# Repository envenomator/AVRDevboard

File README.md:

I bought the book 'Make: AVR Programming - by Elliot Williams' and soon got fed up breadboarding the experiments.
So I created an PCB-based development board for Atmega328p, with basics like 

8x LED on PB0-7
LDR / Potmeter
Servo header / servo power selector 
Two pushbuttons, one at each INT0/1
I2C header 
Serial header 

Several jumpers, to make optimal use of pins.

Selections via jumpers:
1) Use either crystal or LEDs on PB6/7
2) Use either LDR or Potmeter at PC0
3) Use either Servo or LED at PB1 / T1 16-bit timer OC1A
4) Use either VCC voltage for servo, or seperately supplied voltage

PINs available for
1) I2C
2) Serial GND/TX/RX
3) INT0/INT1

Photo shows an earlier PCB with switched labels. Current gerbers are correct and have been printed correctly at JLCPCB.

Enjoy experimenting!

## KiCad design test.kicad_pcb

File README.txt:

A development board for Atmega328p, with basics like 

8x LED on PB0-7
LDR / Potmeter
Servo header / servo power selector 
Two pushbuttons, one at each INT0/1
I2C header 
Serial header 

Several jumpers, to make optimal use of pins.

Selections via jumpers:
1) Use either crystal or LEDs on PB6/7
2) Use either LDR or Potmeter at PC0
3) Use either Servo or LED at PB1 / T1 16-bit timer OC1A
4) Use either VCC voltage for servo, or seperately supplied voltage

PINs available for
1) I2C
2) Serial GND/TX/RX
3) INT0/INT1

Photo shows an earlier PCB with switched labels. Current gerbers are correct and have been printed correctly at JLCPCB.

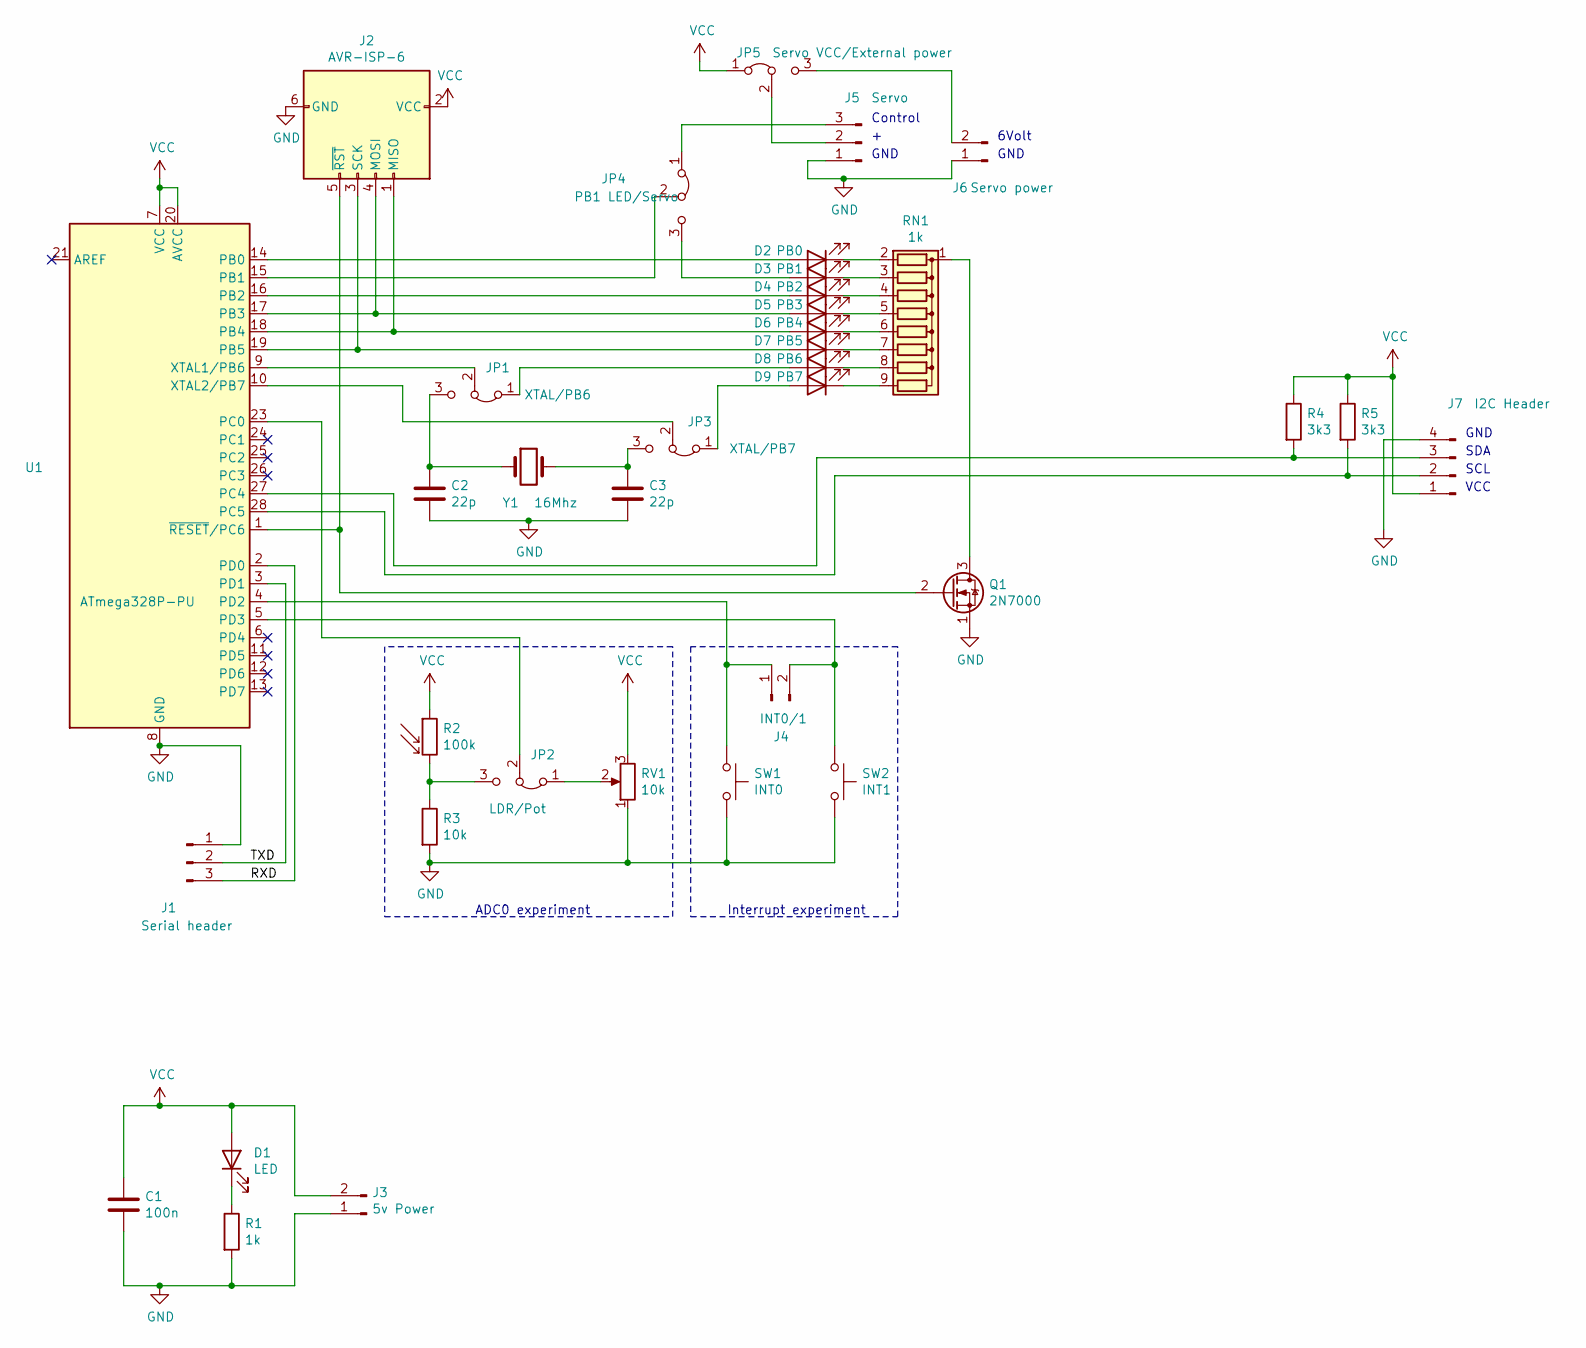
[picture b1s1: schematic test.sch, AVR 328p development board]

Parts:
C1: 100n; C_Disc_D3.4mm_W2.1mm_P2.50mm
C2, C3: 22p; C_Disc_D3.4mm_W2.1mm_P2.50mm
D1: LED; LED_D3.0mm
D2: PB0; LED_D3.0mm
D3: PB1; LED_D3.0mm
D4: PB2; LED_D3.0mm
D5: PB3; LED_D3.0mm
D6: PB4; LED_D3.0mm
D7: PB5; LED_D3.0mm
D8: PB6; LED_D3.0mm
D9: PB7; LED_D3.0mm
J1: Serial header; PinHeader_1x03_P2.54mm_Vertical
J2: AVR-ISP-6; PinHeader_2x03_P2.54mm_Vertical
J3: 5v Power; PinHeader_1x02_P2.54mm_Vertical
J4: INT0/1; PinHeader_1x02_P2.54mm_Vertical
J5: Servo; PinHeader_1x03_P2.54mm_Vertical
J6: Servo power; PinHeader_1x02_P2.54mm_Vertical
J7: I2C Header; PinHeader_1x04_P2.54mm_Vertical
JP1: XTAL/PB6; PinHeader_1x03_P2.54mm_Vertical
JP2: LDR/Pot; PinHeader_1x03_P2.54mm_Vertical
JP3: XTAL/PB7; PinHeader_1x03_P2.54mm_Vertical
JP4: PB1 LED/Servo; PinHeader_1x03_P2.54mm_Vertical
JP5: Servo VCC/External power; PinHeader_1x03_P2.54mm_Vertical
Q1: 2N7000; TO-92_Inline
R1: 1k; R_Axial_DIN0207_L6.3mm_D2.5mm_P7.62mm_Horizontal
R2: 100k; R_Axial_DIN0204_L3.6mm_D1.6mm_P5.08mm_Horizontal
R3: 10k; R_Axial_DIN0207_L6.3mm_D2.5mm_P7.62mm_Horizontal
R4, R5: 3k3; R_Axial_DIN0207_L6.3mm_D2.5mm_P7.62mm_Horizontal
RN1: 1k; R_Array_SIP9
RV1: 10k; Potentiometer_Piher_PT-10-V05_Vertical
SW1: INT0; SW_PUSH_6mm
SW2: INT1; SW_PUSH_6mm
U1: ATmega328P-PU; DIP-28_W7.62mm
Y1: 16Mhz; Crystal_HC18-U_Vertical

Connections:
/RXD: J1.3, U1.2 (PD0)
/TXD: J1.2, U1.3 (PD1)
GND: C1.2, C2.2, C3.2, J1.1, J2.6 (GND), J3.1, J5.1, J6.1, J7.4, Q1.1 (S), R1.2, R3.2, RV1.1, SW1.2, SW2.2, U1.8 (GND), U1.22 (GND)
unnamed: C2.1, JP1.3 (B), Y1.1
unnamed: C3.1, JP3.3 (B), Y1.2
unnamed: D1.1 (K), R1.1
unnamed: D2.1 (K), RN1.2 (R1)
unnamed: D2.2 (A), U1.14 (PB0)
unnamed: D3.1 (K), RN1.3 (R2)
unnamed: D3.2 (A), JP4.3 (B)
unnamed: D4.1 (K), RN1.4 (R3)
unnamed: D4.2 (A), U1.16 (PB2)
unnamed: D5.1 (K), RN1.5 (R4)
unnamed: D5.2 (A), J2.4 (MOSI), U1.17 (PB3)
unnamed: D6.1 (K), RN1.6 (R5)
unnamed: D6.2 (A), J2.1 (MISO), U1.18 (PB4)
unnamed: D7.1 (K), RN1.7 (R6)
unnamed: D7.2 (A), J2.3 (SCK), U1.19 (PB5)
unnamed: D8.1 (K), RN1.8 (R7)
unnamed: D8.2 (A), JP1.1 (A)
unnamed: D9.1 (K), RN1.9 (R8)
unnamed: D9.2 (A), JP3.1 (A)
unnamed: J2.5 (~RST), Q1.2 (G), U1.1 (~RESET~/PC6)
unnamed: J4.1, SW1.1, U1.4 (PD2)
unnamed: J4.2, SW2.1, U1.5 (PD3)
unnamed: J5.2, JP5.2 (C)
unnamed: J5.3, JP4.1 (A)
unnamed: J6.2, JP5.3 (B)
unnamed: J7.2, R5.2, U1.28 (PC5)
unnamed: J7.3, R4.2, U1.27 (PC4)
unnamed: JP1.2 (C), U1.9 (XTAL1/PB6)
unnamed: JP2.1 (A), RV1.2
unnamed: JP2.2 (C), U1.23 (PC0)
unnamed: JP2.3 (B), R2.2, R3.1
unnamed: JP3.2 (C), U1.10 (XTAL2/PB7)
unnamed: JP4.2 (C), U1.15 (PB1)
unnamed: Q1.3 (D), RN1.1 (common)
VCC: C1.1, D1.2 (A), J2.2 (VCC), J3.2, J7.1, JP5.1 (A), R2.1, R4.1, R5.1, RV1.3, U1.7 (VCC), U1.20 (AVCC)

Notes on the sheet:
ADC0 experiment
Interrupt experiment
Control
GND
6Volt
VCC
SCL
SDA

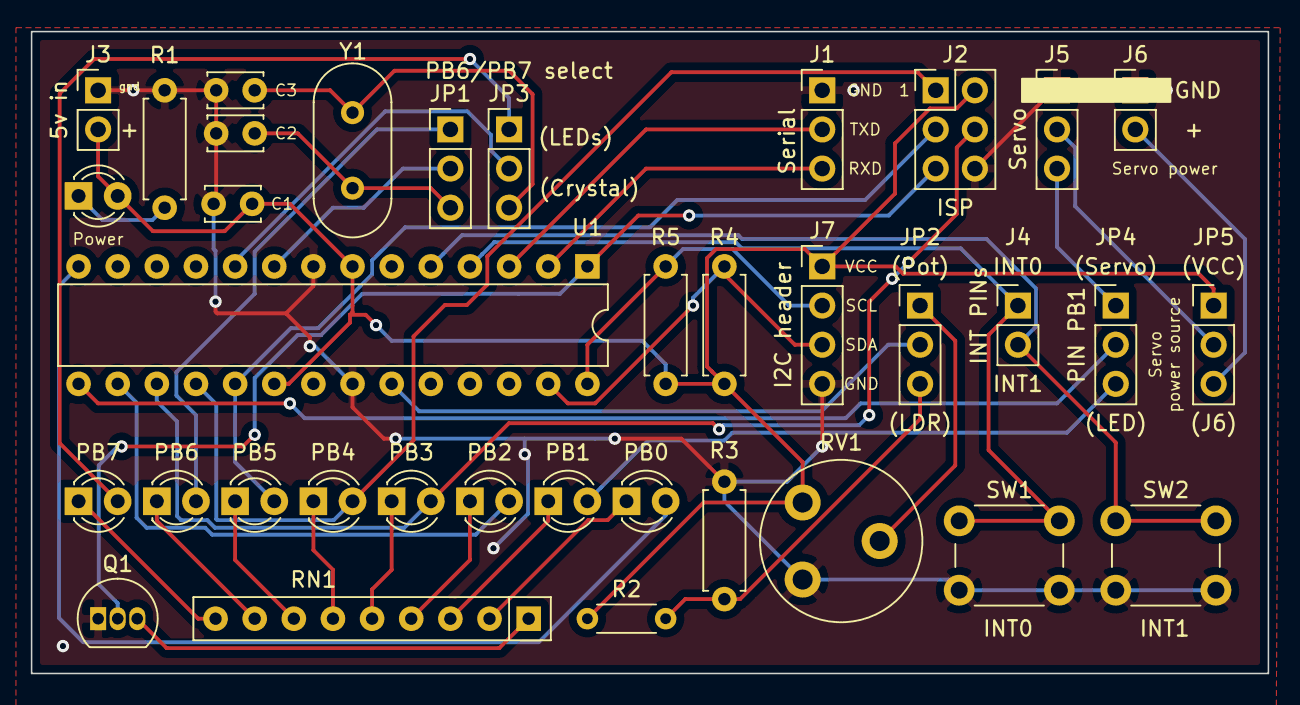
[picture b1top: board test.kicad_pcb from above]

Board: 2 copper layers, 80.3 x 41.7 mm, 36 parts (0 on the bottom side), 38 nets.

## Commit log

2021-01-03 Board as sent to PCBWay
2021-01-03 Changed README content
2021-01-03 Schema error in PD5 fixed, sent to JLCPCB
2021-01-08 Swapped crystal/LED text at JP1/JP3
2021-01-16 Created new Gerbers
2021-01-16 Saved PCB
2021-04-08 Photo and pdf schematic
2021-04-08 Added README

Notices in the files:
test.kicad_pcb:
(c) 2021 Jeroen Venema
